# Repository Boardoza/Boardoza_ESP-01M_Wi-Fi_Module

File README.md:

# Boardoza ESP-01M Wi-Fi Module

The **Boardoza ESP-01M** is a compact, high-performance **Wi-Fi module** based on the **ESP8285** chipset, developed by **Ai Thinker**. It is designed for **IoT applications, smart devices, and wireless communication projects**, offering a fully integrated **802.11 b/g/n (2.4 GHz) Wi-Fi solution** with low power consumption.

The **ESP8285** is an enhanced version of the **ESP8266**, featuring **1MB of embedded flash memory**, allowing it to run standalone applications without requiring an external flash chip. The ESP-01M provides **dual virtual Wi-Fi interfaces** and supports multiple **network modes** (**Station, SoftAP, and Promiscuous mode**), making it a highly flexible choice for **IoT applications**.

## [Click here to purchase!](https://www.ozdisan.com/maker-and-iot-products/boardoza/boardoza-modules/BOARDOZA-ESP01M/1202706)

| Front Side | Back Side |
|:---:|:---:|
|  |  |

---

## **Key Features**

- **ESP8285 SoC**: Fully integrated Wi-Fi solution with **1MB embedded flash**.
- **802.11 b/g/n (2.4 GHz) Wi-Fi**, supporting speeds up to **72.2 Mbps**.
- **Supports AT Command Set** for simple configuration.
- **Low Power Consumption**, ideal for battery-operated devices.
- **UART Communication**, default baud rate **up to 4 Mbps**.
- **Supports Dual Virtual Wi-Fi Interfaces**.
- **Multiple Network Modes**:
  - **Station Mode** (Connects to an Access Point).
  - **SoftAP Mode** (Acts as a Wi-Fi Hotspot).
  - **Promiscuous Mode** (Packet Sniffing & Analysis).
- **Compact Design (20x20mm)**, suitable for space-constrained applications.

---

## **Technical Specifications**

**Model:** ESP-01M (Ai Thinker)

**Chipset:** ESP8285

**Embedded Flash Memory:** 1MB  

**Voltage Supply:** 3.3V - 5V  

**Supported I/O Voltage:** 3.3V

**Functions:** Wi-Fi SoC Module  

**Communication Interface:** UART (up to 4 Mbps)  

**Wi-Fi Standard:** IEEE 802.11b/g/n (2.4 GHz)  

**Max Data Rate:** 72.2 Mbps  

**Network Modes:** Station Mode, SoftAP Mode, Promiscuous Mode  

**Security Protocols:** WPA/WPA2  

**Power Consumption:** Low power operation with deep sleep support  

**Operating Temperature:** -20°C to +85°C  

**Board Dimensions:** 20mm x 20mm  

---

## **Board Pinout**

| Pin Number | Pin Name | Description |
|:---:|:---:|---|
| 1  | 5V  | Positive Power Supply |
| 2  | RST  | External Reset Signal (Active Low for Reset) |
| 3  | TX  | UART Transmit |
| 4  | RX  | UART Receive |
| 5  | IO0  | General Purpose I/O 0 |
| 6  | GND  | Negative Power Supply |

---

## **Board Dimensions**

---

## **Step Files**

[Boardoza ESP-01M.step](./assets/ESP-01M%20Step.step)

---

## **Datasheet**

[Boardoza ESP-01M Datasheet.pdf](./assets/ESP-01M%20Datasheet.pdf)

---

## **Version History**

- V1.0.0 - Initial Release

---

## **Support**

For support and inquiries, contact **<support@boardoza.com>**.

---

## **License**

Shield: [![CC BY-SA 4.0][cc-by-sa-shield]][cc-by-sa]  

This work is licensed under a [Creative Commons Attribution-ShareAlike 4.0 International License][cc-by-sa].  

[![CC BY-SA 4.0][cc-by-sa-image]][cc-by-sa]  

[cc-by-sa]: http://creativecommons.org/licenses/by-sa/4.0/  
[cc-by-sa-image]: https://licensebuttons.net/l/by-sa/4.0/88x31.png  
[cc-by-sa-shield]: https://img.shields.io/badge/License-CC%20BY--SA%204.0-lightgrey.svg

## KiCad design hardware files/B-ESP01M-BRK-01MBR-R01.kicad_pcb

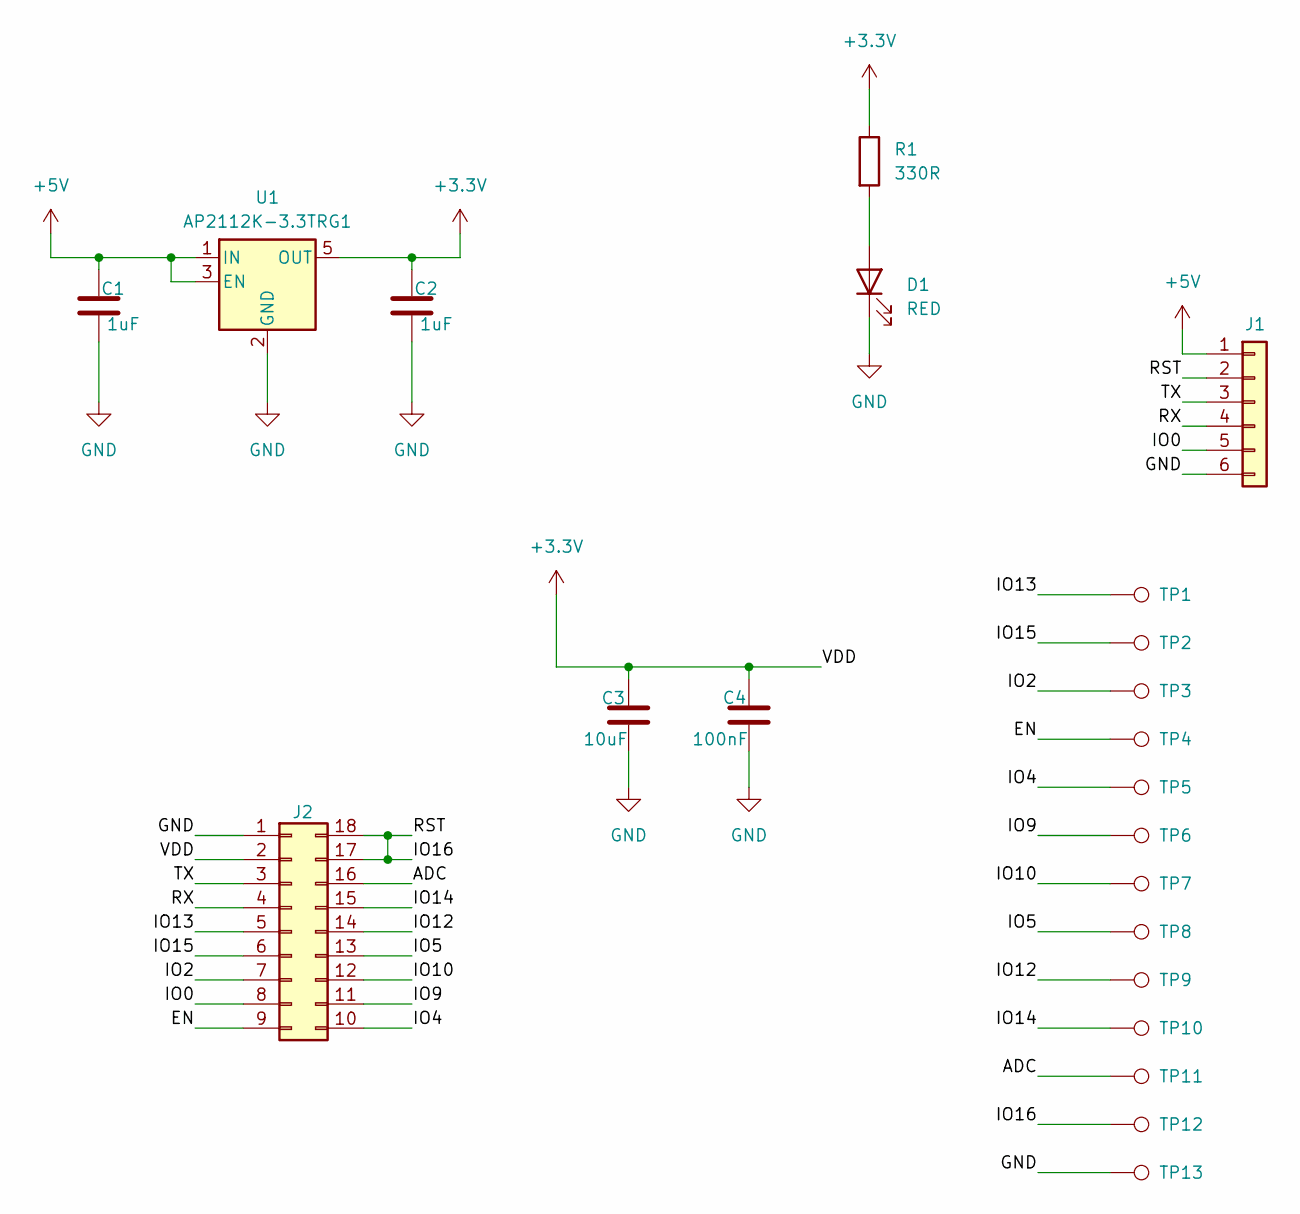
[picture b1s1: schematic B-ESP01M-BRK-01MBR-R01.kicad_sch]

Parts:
C1, C2: 1uF; C_0603_1608Metric
C3: 10uF; C_0603_1608Metric
C4: 100nF; C_0603_1608Metric
D1: RED; LED_0603_1608Metric
J1: Conn_01x06; 2317-06S_1x06_P2.50mm_Vertical
J2: Conn_02x09_Counter_Clockwise; Samtec_HLE-109-02-xxx-DV-BE-A_2x09_P2.54mm_Horizontal
R1: 330R; R_0603_1608Metric
TP1, TP2, TP3, TP4, TP5, TP6, TP7, TP8, TP9, TP10, TP11, TP12, TP13: TestPoint; TestPoint_Pad_1.0x1.0mm
U1: AP2112K-3.3TRG1; SOT-23-5; MPN AP2112K-3.3TRG1

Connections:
+3.3V: C2.1, C3.2, C4.2, J2.2, R1.1, U1.5 (OUT)
+5V: C1.1, J1.1, U1.1 (IN), U1.3 (EN)
/ADC: J2.16, TP11.1
/EN: J2.9, TP4.1
/IO0: J1.5, J2.8
/IO2: J2.7, TP3.1
/IO4: J2.10, TP5.1
/IO5: J2.13, TP8.1
/IO9: J2.11, TP6.1
/IO10: J2.12, TP7.1
/IO12: J2.14, TP9.1
/IO13: J2.5, TP1.1
/IO14: J2.15, TP10.1
/IO15: J2.6, TP2.1
/IO16: J1.2, J2.17, J2.18, TP12.1
/RX: J1.4, J2.4
/TX: J1.3, J2.3
GND: C1.2, C2.2, C3.1, C4.1, D1.1 (K), J1.6, J2.1, TP13.1, U1.2 (GND)
unnamed: D1.2 (A), R1.2

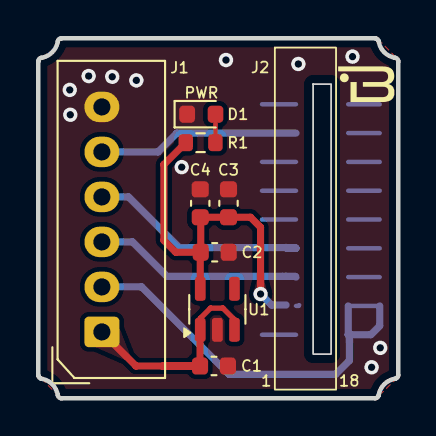
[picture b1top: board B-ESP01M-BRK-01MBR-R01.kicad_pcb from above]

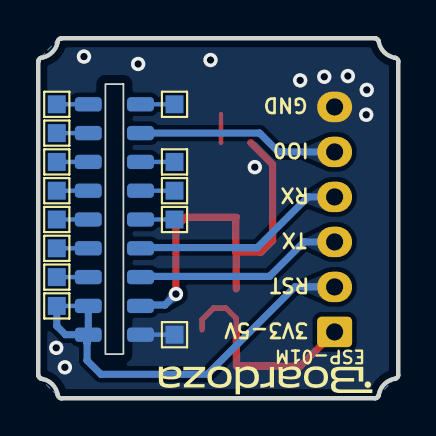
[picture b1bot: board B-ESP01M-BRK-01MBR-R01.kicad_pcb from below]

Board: 2 copper layers, 20.0 x 20.0 mm, 22 parts (13 on the bottom side), 19 nets.

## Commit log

2025-02-18 initial commit for ESP-01M Module
2025-03-17 Update README.md for formatting improvements and additional details
2025-03-24 Add ESP-01M library
2025-11-06 Update UART communication baud rate in README
    Updated UART communication baud rate to reflect maximum speed.
2025-11-06 Add supported I/O voltage information to README
